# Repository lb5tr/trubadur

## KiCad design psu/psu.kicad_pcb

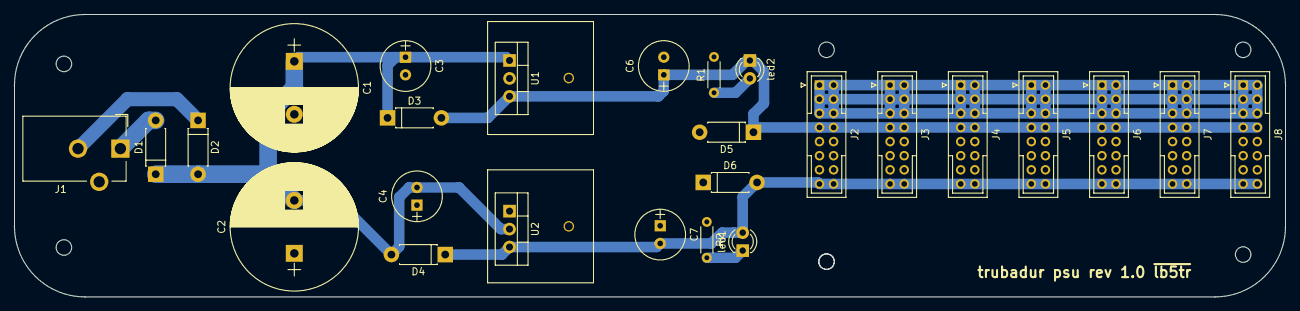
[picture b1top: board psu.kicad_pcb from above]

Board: 2 copper layers, 180.0 x 40.0 mm, 26 parts (0 on the bottom side), 9 nets.

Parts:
C1, C2: 4700u/75V; CP_Radial_D18.0mm_P7.50mm
C3, C4, C6, C7: 1u TAN; CP_Radial_Tantal_D7.0mm_P2.50mm
D1, D2, D3, D4, D5, D6: D; D_DO-41_SOD81_P7.62mm_Horizontal
J1: Jack-DC; Barrel_Jack_CUI_PJ-102AH
J2, J3, J4, J5, J6, J7, J8: Conn_02x08_Odd_Even; JAE_LY20-16P-2T_2x08x2.00mm_Straight_V2
R1, R2: R; R_Axial_DIN0204_L3.6mm_D1.6mm_P5.08mm_Horizontal
U1: LM7812_TO220; TO-220-3_Vertical
U2: LM7912_TO220; TO-220-3_Vertical
led1, led2: LED; LED_D3.0mm

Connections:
+12C: C7.2, D4.1, D6.2, J2.15, J2.16, J3.15, J3.16, J4.15, J4.16, J5.15, J5.16, J6.15, J6.16, J7.15, J7.16, J8.15, J8.16, U2.3, led1.2
+12L: C1.1, C2.2, C3.1, C4.2, D1.1, D2.2, D3.1, D4.2, U1.1, U2.2
+12P: C6.1, D3.2, D5.1, J2.7, J2.8, J3.7, J3.8, J4.7, J4.8, J5.7, J5.8, J6.7, J6.8, J7.7, J7.8, J8.7, J8.8, U1.3, led2.1
GND: C1.2, C2.1, C3.2, C4.1, C6.2, C7.1, D5.2, D6.1, J1.3, J2.9, J2.10, J2.11, J2.12, J2.13, J2.14, J3.9, J3.10, J3.11, J3.12, J3.13, J3.14, J4.9, J4.10, J4.11, J4.12, J4.13, J4.14, J5.9, J5.10, J5.11, J5.12, J5.13, J5.14, J6.9, J6.10, J6.11, J6.12, J6.13, J6.14, J7.9, J7.10, J7.11, J7.12, J7.13, J7.14, J8.9, J8.10, J8.11, J8.12, J8.13, J8.14, R1.2, R2.1, U1.2, U2.1
unnamed: D1.2, J1.1
unnamed: D2.1, J1.2
unnamed: J2.1, J2.2, J2.3, J2.4, J2.5, J2.6, J3.1, J3.2, J3.3, J3.4, J3.5, J3.6, J4.1, J4.2, J4.3, J4.4, J4.5, J4.6, J5.1, J5.2, J5.3, J5.4, J5.5, J5.6, J6.1, J6.2, J6.3, J6.4, J6.5, J6.6, J7.1, J7.2, J7.3, J7.4, J7.5, J7.6, J8.1, J8.2, J8.3, J8.4, J8.5, J8.6
unnamed: R1.1, led2.2
unnamed: R2.2, led1.1

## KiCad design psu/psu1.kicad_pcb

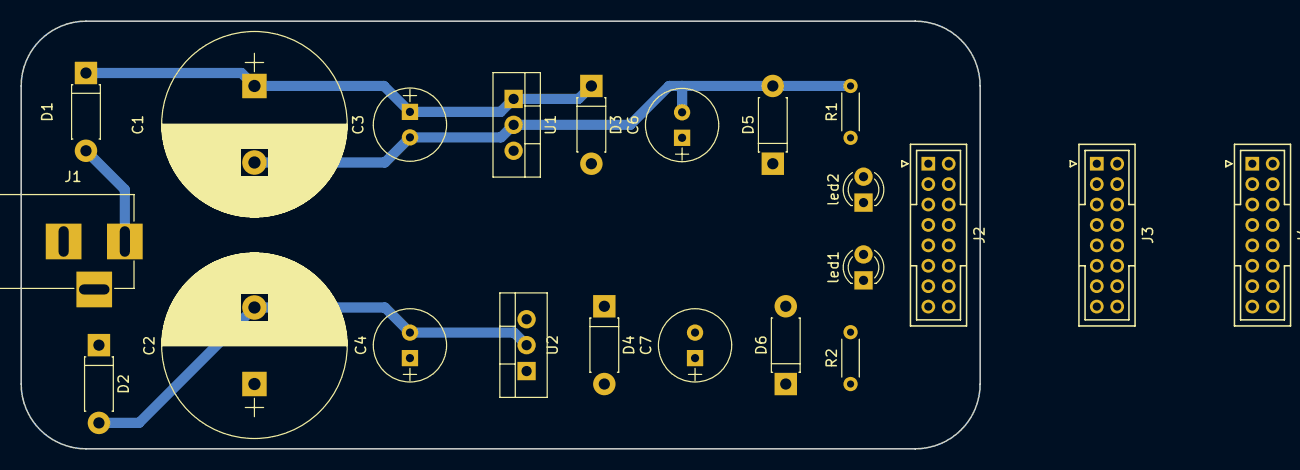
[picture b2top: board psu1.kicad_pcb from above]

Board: 2 copper layers, 94.0 x 41.9 mm, 22 parts (0 on the bottom side), 15 nets.

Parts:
C1, C2: 4700u/75V; CP_Radial_D18.0mm_P7.50mm
C3, C4, C6, C7: 1u TAN; CP_Radial_Tantal_D7.0mm_P2.50mm
D1, D2, D3, D4, D5, D6: D; D_DO-41_SOD81_P7.62mm_Horizontal
J1: Jack-DC; BARREL_JACK
J2, J3, J4: Conn_02x08_Odd_Even; JAE_LY20-16P-2T_2x08x2.00mm_Straight
R1, R2: R; R_Axial_DIN0204_L3.6mm_D1.6mm_P5.08mm_Horizontal
U1: LM7812_TO220; TO-220-3_Vertical
U2: LM7912_TO220; TO-220-3_Vertical
led1, led2: LED; LED_D3.0mm

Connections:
GND: C1.2, C2.1, C3.2, C4.1, C6.2, C7.1, D2.1, D5.2, D6.1, J1.3, J2.9, J2.11, J2.13, R1.2, R2.1, U1.2, U2.1
unnamed: C1.1, C3.1, D1.1, D3.1, U1.1
unnamed: C2.2, C4.2, D2.2, D4.2, U2.2
unnamed: C6.1, D3.2, D5.1, J2.7, U1.3, led2.1
unnamed: C7.2, D4.1, D6.2, J2.15, J2.16, J3.15, J3.16, J4.15, J4.16, U2.3, led1.2
unnamed: D1.2, J1.1
unnamed: J2.1, J2.2, J3.1, J3.2, J4.1, J4.2
unnamed: J2.3, J2.4, J3.3, J3.4, J4.3, J4.4
unnamed: J2.5, J2.6, J3.5, J3.6, J4.5, J4.6
unnamed: J2.8, J3.7
unnamed: J2.10, J2.12, J2.14, J3.9, J3.11, J3.13
unnamed: J3.8, J4.7
unnamed: J3.10, J3.12, J3.14, J4.9, J4.10, J4.11, J4.12, J4.13, J4.14
unnamed: R1.1, led2.2
unnamed: R2.2, led1.1

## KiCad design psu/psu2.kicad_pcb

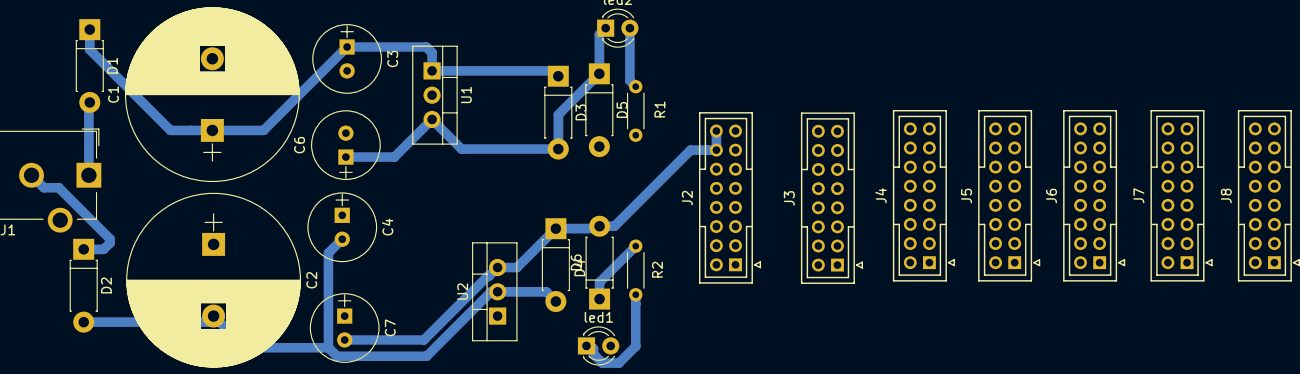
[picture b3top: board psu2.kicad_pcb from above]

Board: 2 copper layers, 26 parts (0 on the bottom side), 37 nets.

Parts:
C1, C2: 4700u/75V; CP_Radial_D18.0mm_P7.50mm
C3, C4, C6, C7: 1u TAN; CP_Radial_Tantal_D7.0mm_P2.50mm
D1, D2, D3, D4, D5, D6: D; D_DO-41_SOD81_P7.62mm_Horizontal
J1: Jack-DC; Barrel_Jack_CUI_PJ-102AH
J2, J3, J4, J5, J6, J7, J8: Conn_02x08_Odd_Even; JAE_LY20-16P-2T_2x08x2.00mm_Straight
R1, R2: R; R_Axial_DIN0204_L3.6mm_D1.6mm_P5.08mm_Horizontal
U1: LM7812_TO220; TO-220-3_Vertical
U2: LM7912_TO220; TO-220-3_Vertical
led1, led2: LED; LED_D3.0mm

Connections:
+12C: C7.2, D4.1, D6.2, J2.15, J2.16, J3.15, J3.16, J4.15, J4.16, J5.15, U2.3, led1.2
+12L: C1.1, C2.2, C3.1, C4.2, D1.1, D2.2, D3.1, D4.2, U1.1, U2.2
+12P: C6.1, D3.2, D5.1, J2.7, U1.3, led2.1
GND: C1.2, C2.1, C3.2, C4.1, C6.2, C7.1, D5.2, D6.1, J1.3, J2.9, J2.11, J2.13, R1.2, R2.1, U1.2, U2.1
unnamed: D1.2, J1.1
unnamed: D2.1, J1.2
unnamed: J2.1, J2.2, J3.1, J3.2, J4.1, J4.2, J5.1
unnamed: J2.3, J2.4, J3.3, J3.4, J4.3, J4.4, J5.3
unnamed: J2.5, J2.6, J3.5, J3.6, J4.5, J4.6, J5.5
unnamed: J2.8, J3.7
unnamed: J2.10, J2.12, J2.14, J3.9, J3.11, J3.13
unnamed: J3.8, J4.7
unnamed: J3.10, J3.12, J3.14, J4.9, J4.10, J4.11, J4.12, J4.13, J4.14, J5.9, J5.11, J5.13
unnamed: J4.8, J5.7
unnamed: J5.2, J6.1
unnamed: J5.4, J6.3
unnamed: J5.6, J6.5
unnamed: J5.8, J6.7
unnamed: J5.10, J5.12, J5.14, J6.9, J6.11, J6.13
unnamed: J5.16, J6.15
unnamed: J6.2, J7.1
unnamed: J6.4, J7.3
unnamed: J6.6, J7.5
unnamed: J6.8, J7.7
unnamed: J6.10, J7.9
unnamed: J6.12, J7.11
unnamed: J6.14, J7.13
unnamed: J6.16, J7.15
unnamed: J7.2, J8.1
unnamed: J7.4, J8.3
unnamed: J7.6, J8.5
unnamed: J7.10, J8.9
unnamed: J7.12, J8.11
unnamed: J7.14, J8.13
unnamed: J7.16, J8.15
unnamed: R1.1, led2.2
unnamed: R2.2, led1.1

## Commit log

2018-08-13 init
